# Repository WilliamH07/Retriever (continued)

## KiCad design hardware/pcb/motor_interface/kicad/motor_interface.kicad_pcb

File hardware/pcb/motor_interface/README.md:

# motor_interface

> **v2.0-draft — do not fabricate before M7, HALL_OC, P1, P2, P3.** Schematic and
> layout generated, ERC and DRC clean (ERC 0, DRC 0 with schematic parity and all severities, 0 unconnected). Every choice and its reason:
> [`decisions.md`](decisions.md) (French). Brief:
> [`cahier-des-charges.md`](cahier-des-charges.md).

| | |
|---|---|
| Size | 100 × 100 mm, 4 layers, 4 × M3, antenna notch on the right edge |
| Parts | 123 placed by the assembler (117 SMD + 6 Micro-Fit 6-way); hand-soldered: 2 × Micro-Fit 8-way, 2 × Mill-Max sockets; 14 option footprints not fitted; 20 named test pads |
| Module | ESP32-DevKitC V4 on two 1 × 19 turned-pin sockets, rows 25.40 mm apart (P1 to confirm) |
| Sources | [`kicad/`](kicad/) — KiCad 10 project, **generated** by [`scripts/build.py`](scripts/build.py) |
| Fabrication | [`fab/`](fab/) — Gerber zip, JLCPCB BOM and placement, schematic PDF, renders |

Rebuild everything: `./build.sh` (routing takes several minutes) then `./fab.sh`
(needs the toolchain in [`../outils.md`](../outils.md)). Do not edit the KiCad files
by hand: change `scripts/build.py` and rebuild.

Sits between a MOTION ESP32 and two ZS-X11H drivers with their hub motors. One
reference, two boards in service (front and rear), three spares from a lot of five.
The role is set by a solder jumper read through the ADS1115, not by GPIO straps.

The specification of record is
[`10-spec-motor-interface.md`](../../../docs/architecture/10-spec-motor-interface.md).
The earlier four-motor board is archived in
[`docs/archive/pcb-v1/`](../../../docs/archive/pcb-v1/).

## What changed against the specification (13 November 2026)

| Point | Spec / ICD v1.2 | This board | Why |
|---|---|---|---|
| `5V_BRAKE` | through J5/J6 pin 7, 2200 µF on board | **not on this board**, pin 7 NC | Decision D5: unplugging the board must keep the brake applied |
| Power input | J7 and trunk pin 1 | **trunk only**, J7 removed | One source, nothing to arbitrate |
| Grounds | undefined | **`GND`, `GND_MOT_A`, `GND_MOT_B` kept apart**, bench-only 0 Ω ties not fitted | Decision D4: single star point on `safety_power` |
| DAC supply | 5 V | **3.3 V**, internal 2.048 V reference, op-amp gain 2.5 | `MCP4728` VIH = 0.7 VDD, unreachable from a 3.3 V bus at 5 V |
| Low-side switches | `DMG1012T` (SOT-523) | **`AO3400A`** (SOT-23, JLCPCB basic) | 48 mΩ guaranteed at VGS 2.5 V, hand-reworkable |
| Polarity options | on `DIR`, `STOP`, `EL` | **`DIR` and `STOP` only** | Any option on `EL` could defeat the fail-safe |
| Hall PPTC | 30 mA on the pull-up tap | **removed** | Separate `+5V_MOT_A/B` nets; no PPTC of that size trips before the 78L05 |
| Hall activity LEDs | six | **none** | Test points and the serial console do the same job |

## Scope

| Function | Implementation |
|---|---|
| Hall passthrough | J1→J3, J2→J4: five straight 0.8 mm tracks each, one layer, no via, no part in series |
| Hall tap | 2.2 kΩ pull-up (population option, HALL_OC), 2.2 kΩ + 10 nF / 100 V, `BAT54S` clamp, referenced to `GND_MOT_x`; `SN74LVC3G17` at 3.3 V (Ioff) |
| Speed command | `MCP4728` (3.3 V, internal ref.) → `TLV9062` ×2.5 → `VR`, 0 V with the module out |
| `DIR`, `STOP` | `AO3400A` open drain, gate pull-down; pull-up / pull-down / direct-drive footprints not fitted |
| Brake `EL` | per wheel `74LVC1G08` (`GPIO26` AND `/SAFE`) → `AO3400A`; pull-up on the harness |
| Temperatures, role, revision | `ADS1115` at 0x48: NTC A, NTC B, role divider (SJ1/SJ2), revision divider (½ = v2.0) |
| Watchdog | `TPL5010`, 2 s, `RSTn` on the module `EN` (D7) |
| CAN | `TCAN1042HVDR`, `STB` grounded, `VIO` 3.3 V, `NUP2105L`, `ACT45B`, no termination |
| Power | trunk 5 V → `AO3401A` reverse protection → `SMAJ6.0A` → `LM66100` → module 5 V; 3.3 V from the module |

## Blocking measurements

M7 (Hall output level and impedance), HALL_OC (open collector or push-pull),
HALL_COL (wire colours, silkscreen), P1 to P3 on the ESP32 module (row spacing, pin
order, PSRAM variant). See [`docs/measurements/`](../../../docs/measurements/).

Pinout: `boards.motor_interface` in [`hardware/icd.yaml`](../../icd.yaml) (v1.3; the
changes this board brought to v1.3 are listed at the end of [`decisions.md`](decisions.md)).

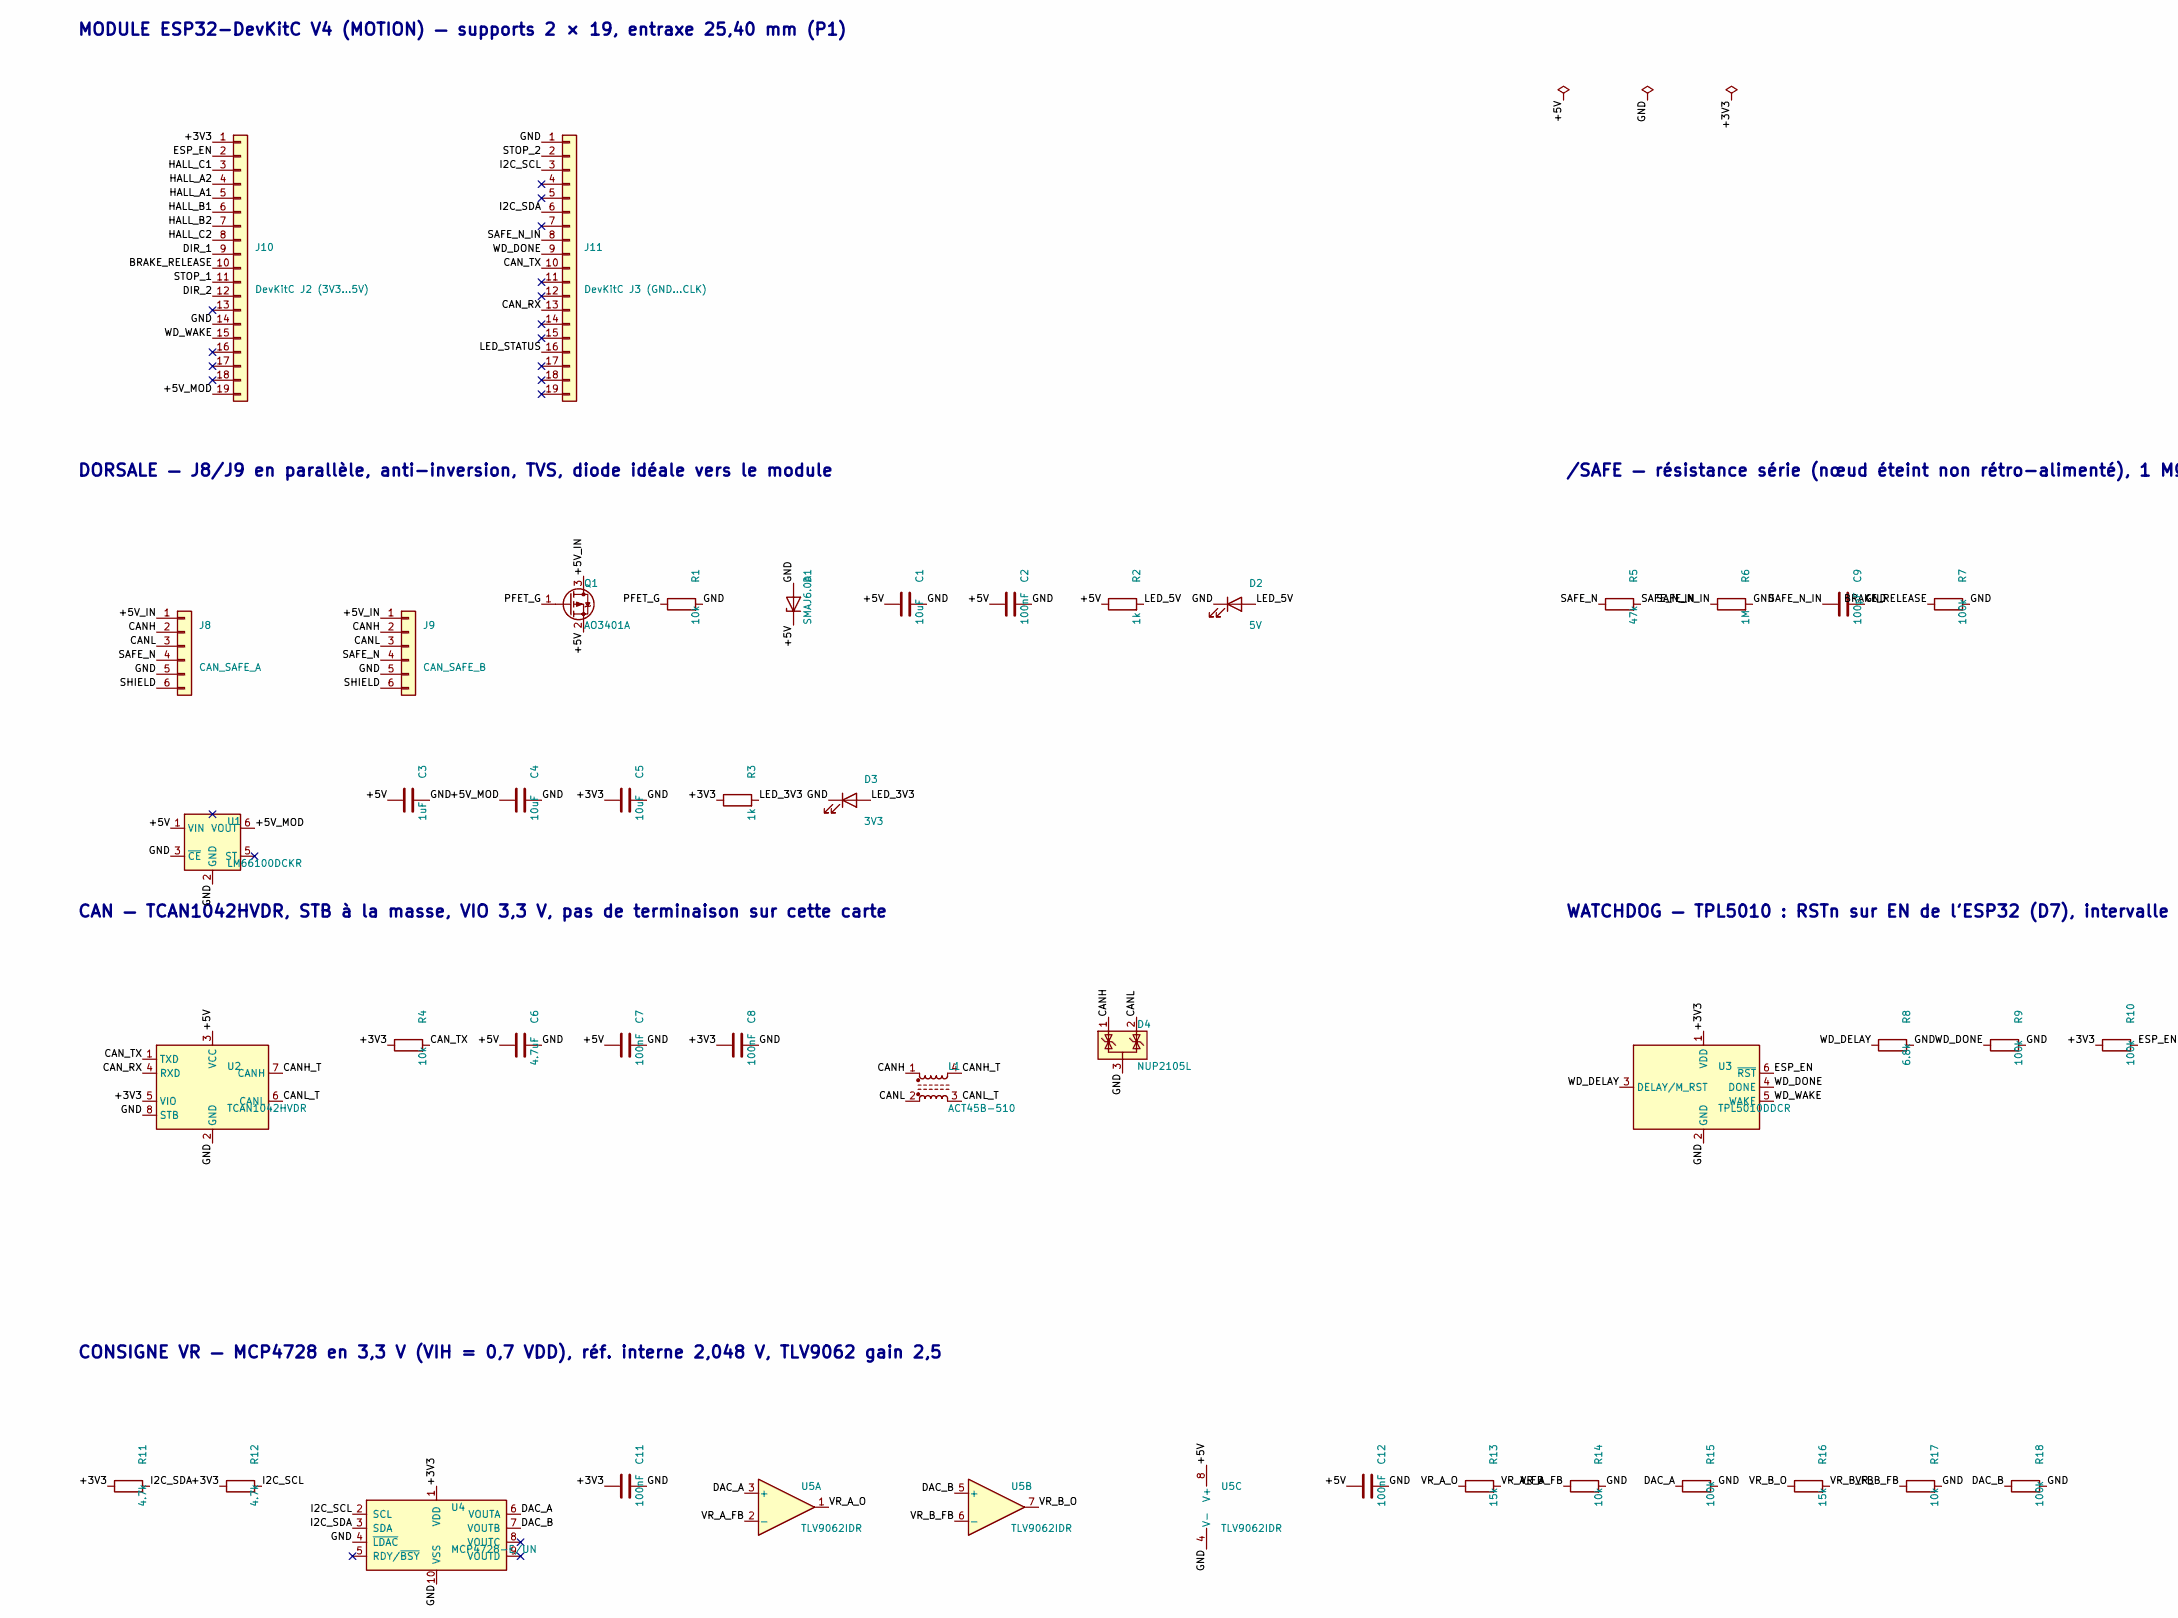
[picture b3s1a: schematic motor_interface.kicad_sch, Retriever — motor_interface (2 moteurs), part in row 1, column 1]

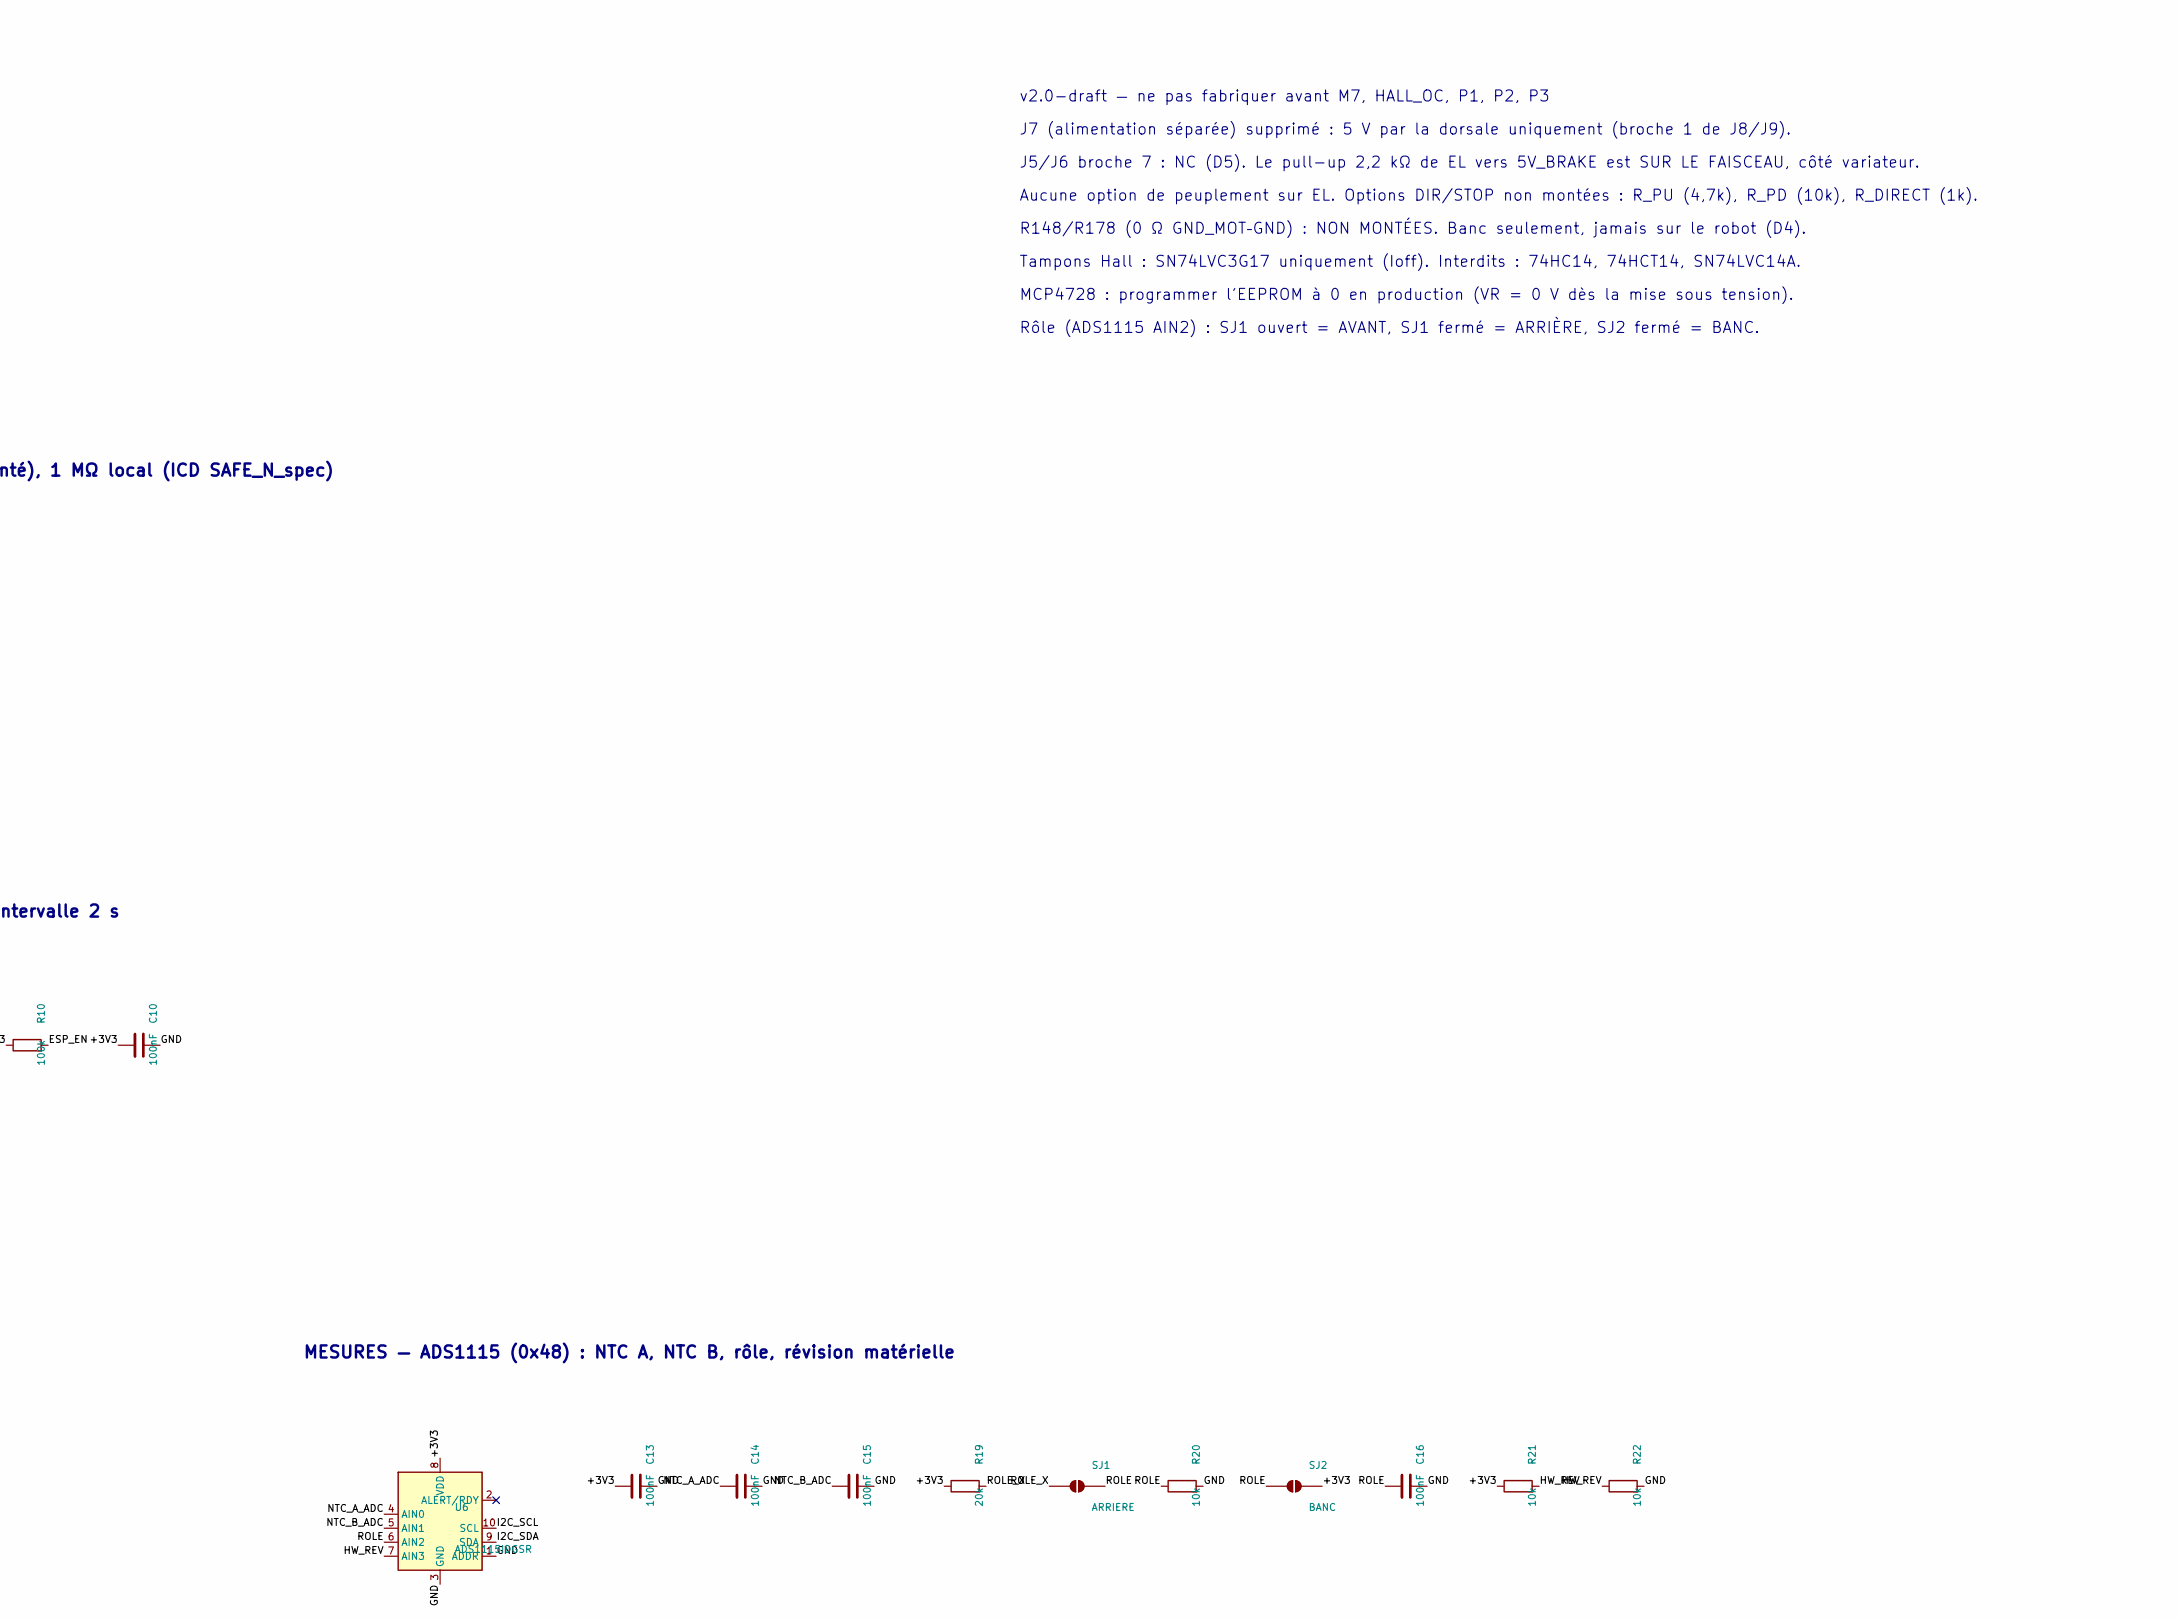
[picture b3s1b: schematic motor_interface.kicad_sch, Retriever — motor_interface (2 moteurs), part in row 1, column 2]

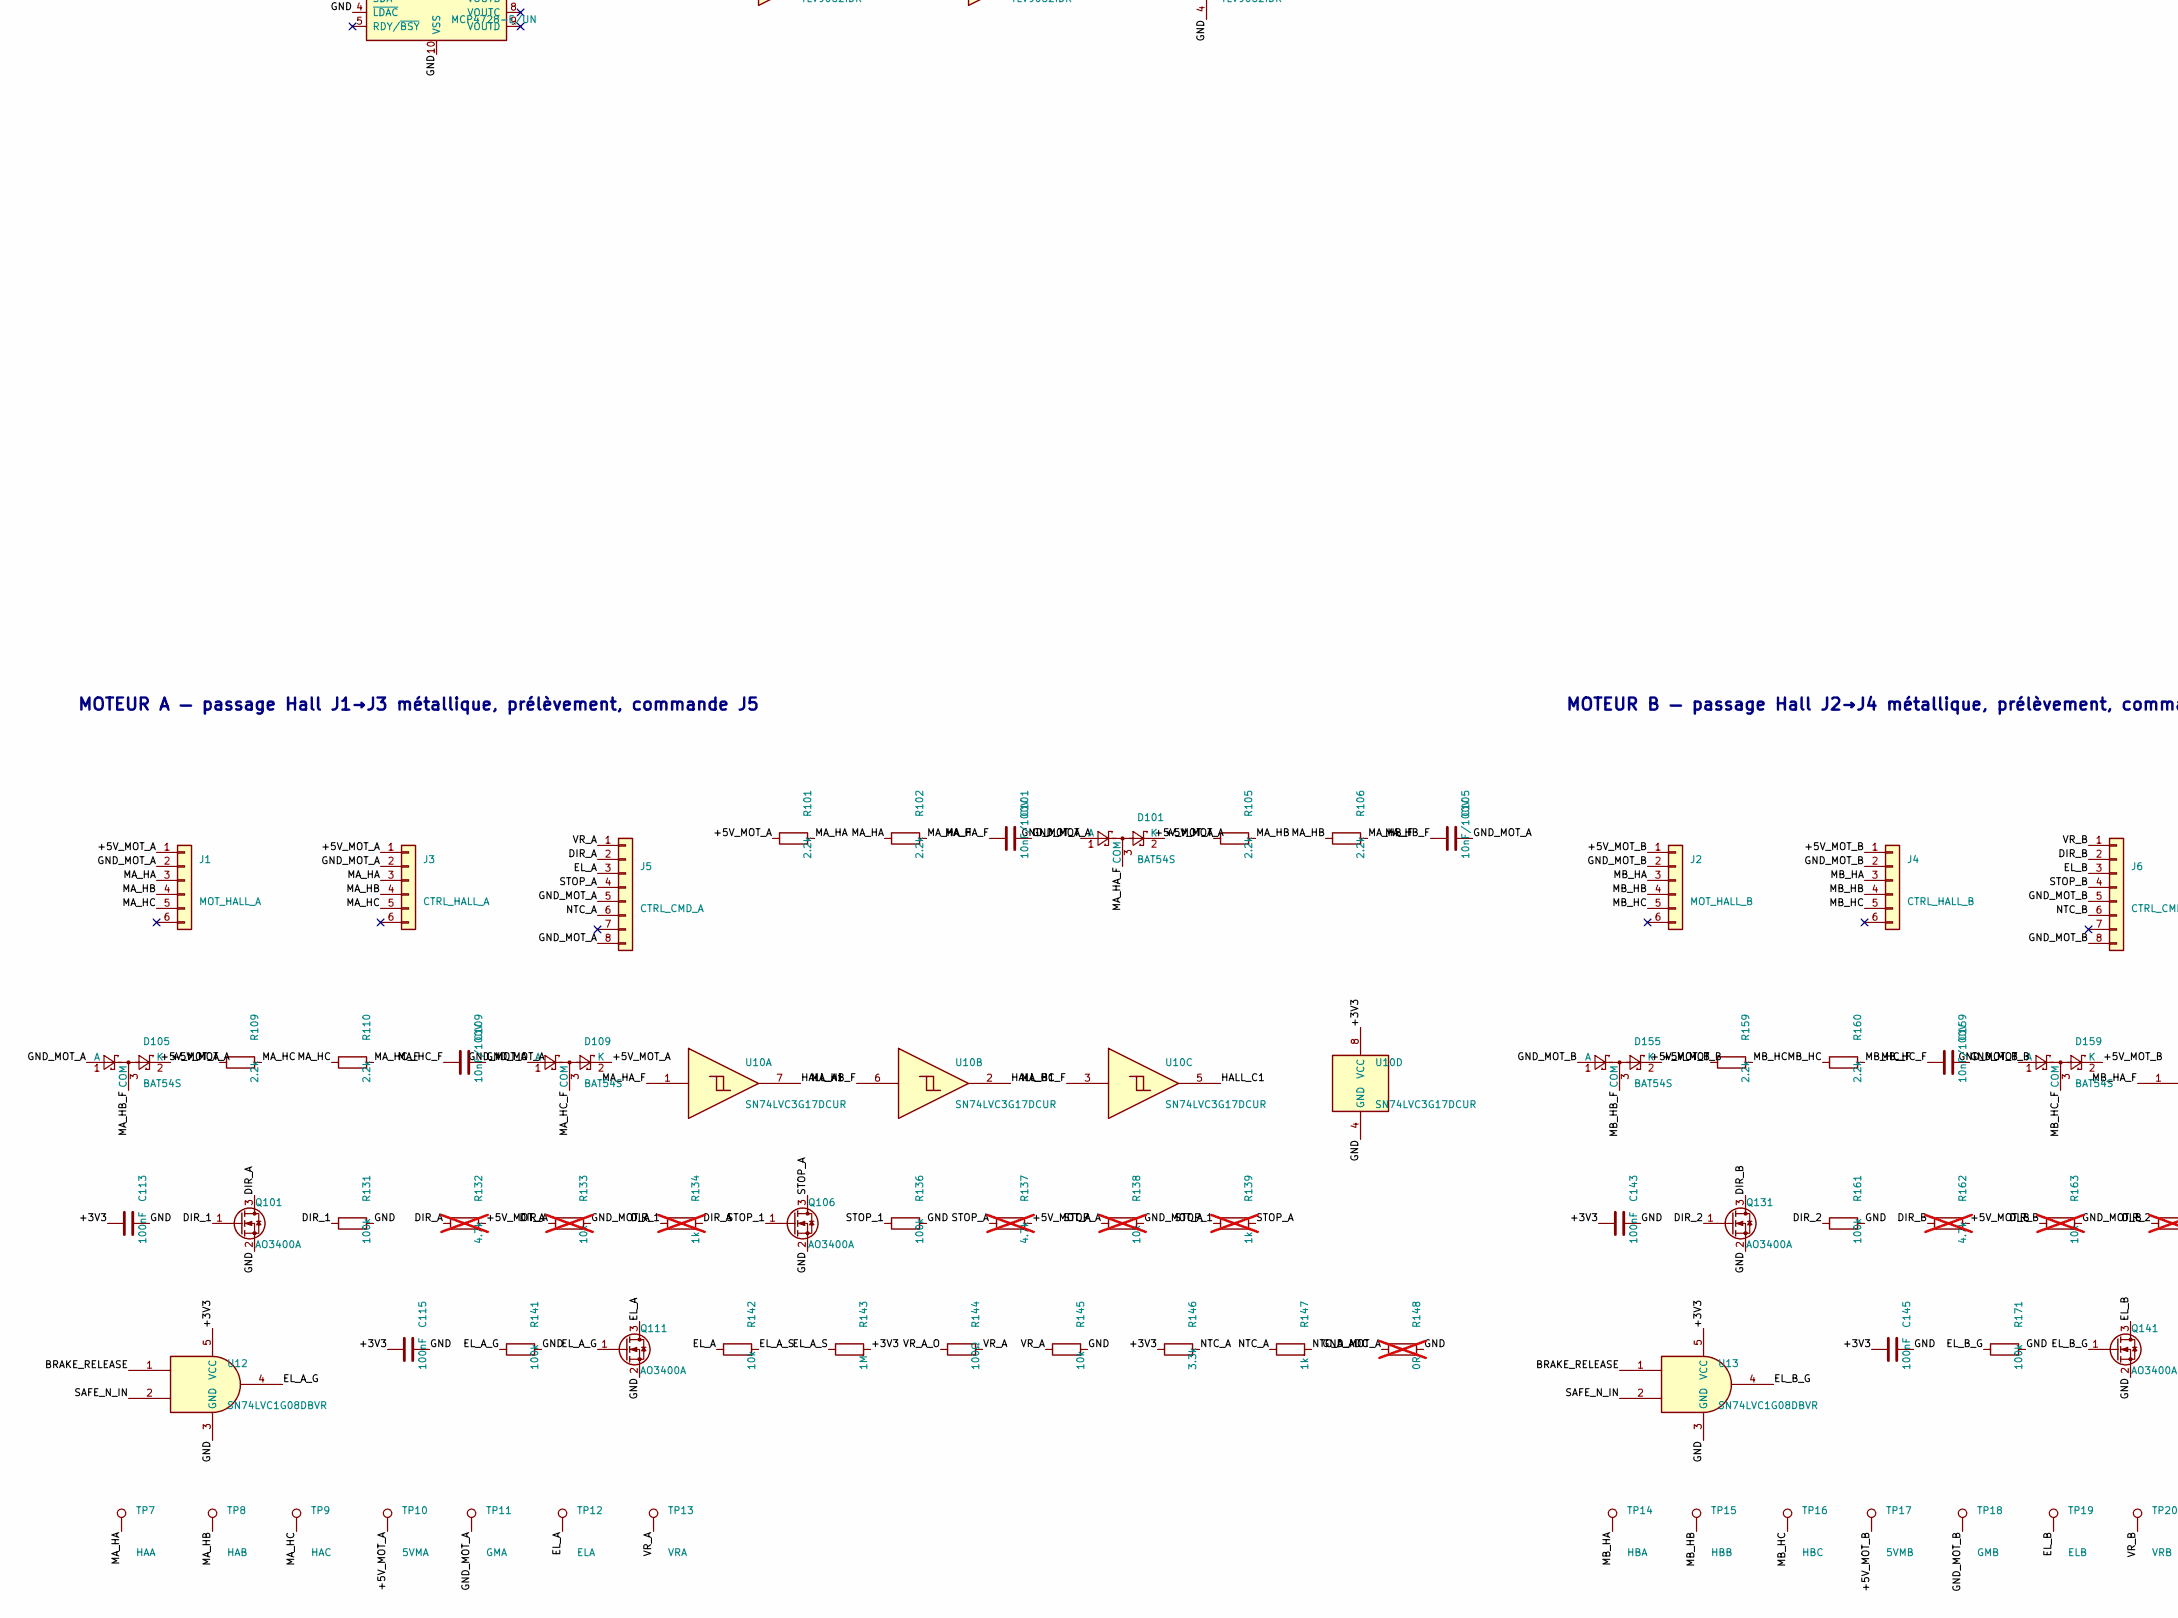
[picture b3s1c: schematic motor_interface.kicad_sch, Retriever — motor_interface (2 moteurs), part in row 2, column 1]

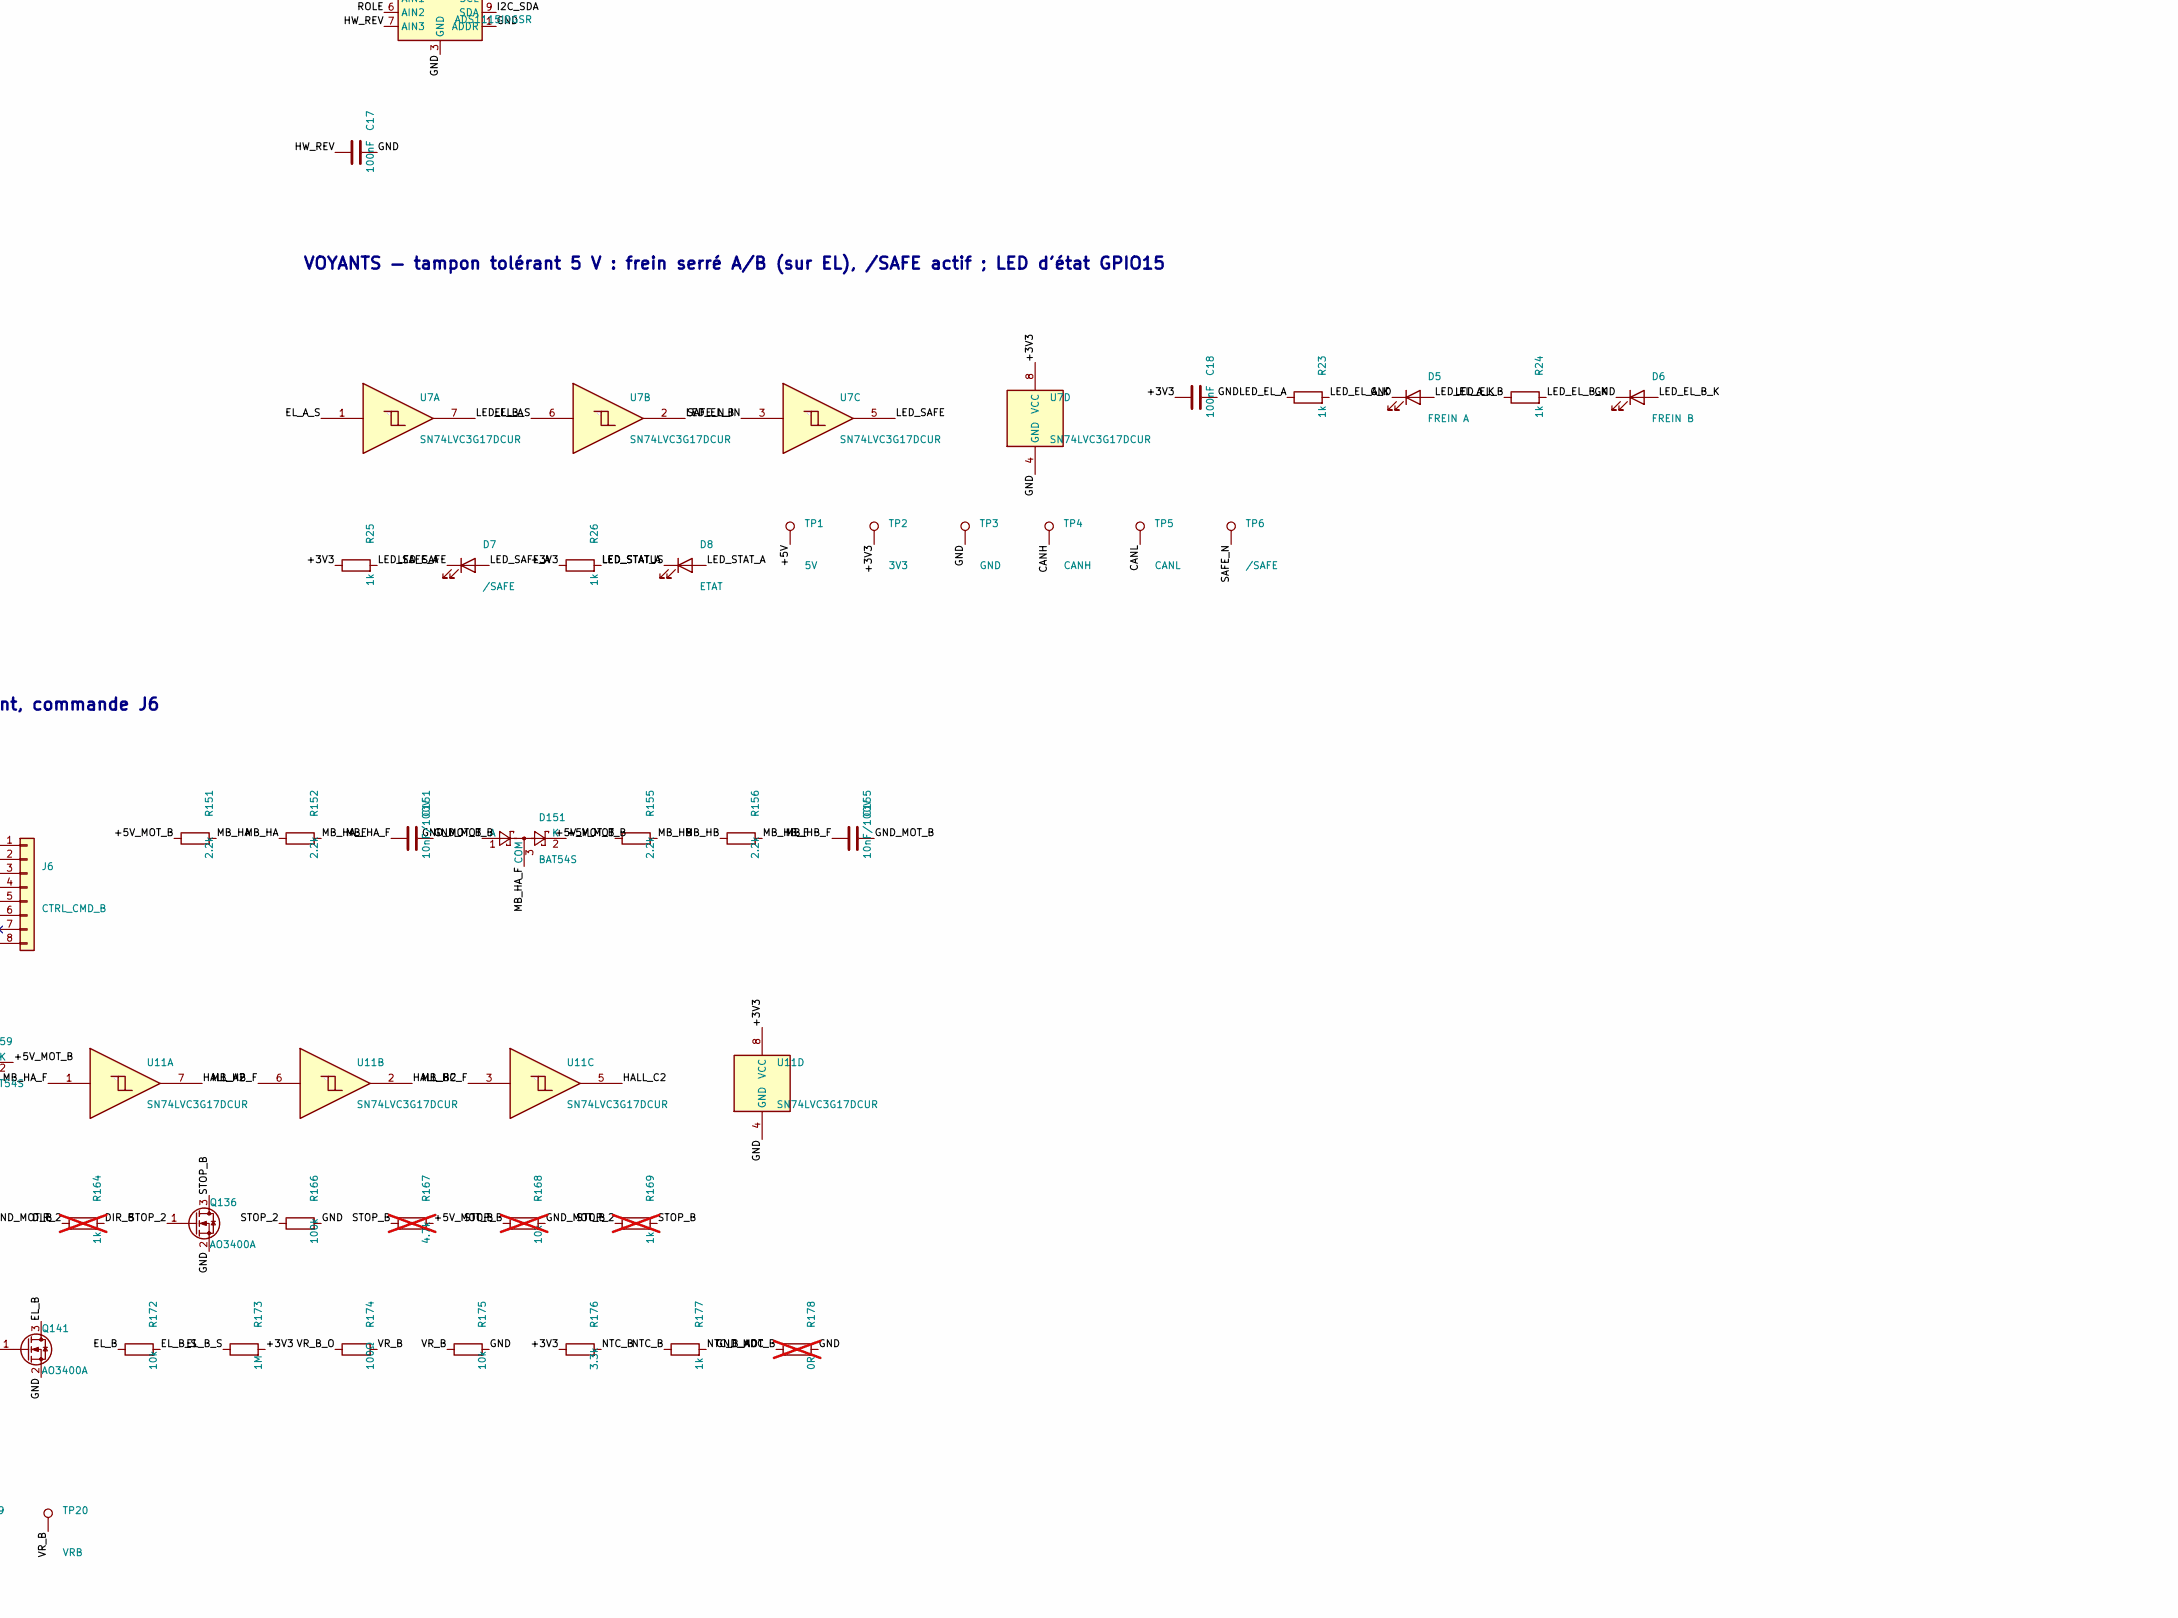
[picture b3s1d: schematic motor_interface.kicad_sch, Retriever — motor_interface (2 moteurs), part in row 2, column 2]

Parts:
C1, C4, C5: 10uF; C_0805_2012Metric; MPN CL21A106KAYNNNE; LCSC C15850
C2, C7, C8, C10, C11, C12, C13, C14, C15, C16, C17, C18, C113, C115, C143, C145: 100nF; C_0603_1608Metric; MPN CC0603KRX7R9BB104; LCSC C14663
C3: 1uF; C_0603_1608Metric; MPN CL10A105KB8NNNC; LCSC C15849
C6: 4.7uF; C_0805_2012Metric; MPN CL21A475KAQNNNE; LCSC C1779
C9: 100pF; C_0603_1608Metric; MPN CC0603JRNPO9BN101; LCSC C14858
C101, C105, C109, C151, C155, C159: 10nF/100V; C_0603_1608Metric; MPN FH 0603B103K101NT; LCSC C43253
D1: SMAJ6.0A; D_SMA; MPN Littelfuse SMAJ6.0A; LCSC C223993
D2: 5V; LED_0603_1608Metric; MPN Everlight 19-217/GHC; LCSC C72043
D3: 3V3; LED_0603_1608Metric; MPN Everlight 19-217/GHC; LCSC C72043
D4: NUP2105L; SOT-23; MPN onsemi NUP2105LT1G; LCSC C14486
D5: FREIN A; LED_0603_1608Metric; MPN Hubei KENTO KT-0603R; LCSC C2286
D6: FREIN B; LED_0603_1608Metric; MPN Hubei KENTO KT-0603R; LCSC C2286
D7: /SAFE; LED_0603_1608Metric; MPN Hubei KENTO KT-0603R; LCSC C2286
D8: ETAT; LED_0603_1608Metric; MPN Everlight 19-217/BHC; LCSC C72041
D101, D105, D109, D151, D155, D159: BAT54S; SOT-23; MPN Nexperia BAT54S,215; LCSC C47546
J1: MOT_HALL_A; Molex_Micro-Fit_3.0_43650-0615_1x06_P3.00mm_Vertical; MPN Molex 43650-0615; LCSC C505231
J2: MOT_HALL_B; Molex_Micro-Fit_3.0_43650-0615_1x06_P3.00mm_Vertical; MPN Molex 43650-0615; LCSC C505231
J3: CTRL_HALL_A; Molex_Micro-Fit_3.0_43650-0615_1x06_P3.00mm_Vertical; MPN Molex 43650-0615; LCSC C505231
J4: CTRL_HALL_B; Molex_Micro-Fit_3.0_43650-0615_1x06_P3.00mm_Vertical; MPN Molex 43650-0615; LCSC C505231
J5: CTRL_CMD_A; Molex_Micro-Fit_3.0_43650-0815_1x08_P3.00mm_Vertical; MPN Molex 43650-0815 (Mouser 538-43650-0815)
J6: CTRL_CMD_B; Molex_Micro-Fit_3.0_43650-0815_1x08_P3.00mm_Vertical; MPN Molex 43650-0815 (Mouser 538-43650-0815)
J8: CAN_SAFE_A; Molex_Micro-Fit_3.0_43650-0615_1x06_P3.00mm_Vertical; MPN Molex 43650-0615; LCSC C505231
J9: CAN_SAFE_B; Molex_Micro-Fit_3.0_43650-0615_1x06_P3.00mm_Vertical; MPN Molex 43650-0615; LCSC C505231
J10: DevKitC J2 (3V3…5V); PinSocket_1x19_P2.54mm_Vertical; MPN Mill-Max 310-43-119-41-001000 (Mouser)
J11: DevKitC J3 (GND…CLK); PinSocket_1x19_P2.54mm_Vertical; MPN Mill-Max 310-43-119-41-001000 (Mouser)
L1: ACT45B-510; IND-SMD_4P-L4.5-W3.2-TL; MPN TDK ACT45B-510-2P-TL003; LCSC C76584
Q1: AO3401A; SOT-23; MPN AOS AO3401A; LCSC C15127
Q101, Q106, Q111, Q131, Q136, Q141: AO3400A; SOT-23; MPN AOS AO3400A; LCSC C20917
R1, R4, R14, R17, R20, R21, R22, R142, R145, R172, R175: 10k; R_0603_1608Metric; MPN 0603WAF1002T5E; LCSC C25804
R2, R3, R23, R24, R25, R26, R147, R177: 1k; R_0603_1608Metric; MPN 0603WAF1001T5E; LCSC C21190
R5: 47k; R_0603_1608Metric; MPN 0603WAF4702T5E; LCSC C25819
R6, R143, R173: 1M; R_0603_1608Metric; MPN 0603WAF1004T5E; LCSC C22935
R7, R9, R10, R15, R18, R131, R136, R141, R161, R166, R171: 100k; R_0603_1608Metric; MPN 0603WAF1003T5E; LCSC C25803
R8: 6.8k; R_0603_1608Metric; MPN 0603WAF6801T5E; LCSC C23212
R11, R12: 4.7k; R_0603_1608Metric; MPN 0603WAF4701T5E; LCSC C23162
R13, R16: 15k; R_0603_1608Metric; MPN 0603WAF1502T5E; LCSC C22809
R19: 20k; R_0603_1608Metric; MPN 0603WAF2002T5E; LCSC C4184
R101, R102, R105, R106, R109, R110, R151, R152, R155, R156, R159, R160: 2.2k; R_0603_1608Metric; MPN 0603WAF2201T5E; LCSC C4190
R132, R137, R162, R167: 4.7k; R_0603_1608Metric; MPN 0603WAF4701T5E; LCSC C23162; not fitted
R133, R138, R163, R168: 10k; R_0603_1608Metric; MPN 0603WAF1002T5E; LCSC C25804; not fitted
R134, R139, R164, R169: 1k; R_0603_1608Metric; MPN 0603WAF1001T5E; LCSC C21190; not fitted
R144, R174: 100Ω; R_0603_1608Metric; MPN 0603WAF1000T5E; LCSC C22775
R146, R176: 3.3k; R_0603_1608Metric; MPN 0603WAF3301T5E; LCSC C22978
R148, R178: 0R; R_0603_1608Metric; MPN 0603WAF0000T5E; LCSC C21189; not fitted
SJ1: ARRIERE; SolderJumper-2_P1.3mm_Open_RoundedPad1.0x1.5mm
SJ2: BANC; SolderJumper-2_P1.3mm_Open_RoundedPad1.0x1.5mm
TP1: 5V; TestPoint_Pad_D1.5mm
TP2: 3V3; TestPoint_Pad_D1.5mm
TP3: GND; TestPoint_Pad_D1.5mm
TP4: CANH; TestPoint_Pad_D1.5mm
TP5: CANL; TestPoint_Pad_D1.5mm
TP6: /SAFE; TestPoint_Pad_D1.5mm
TP7: HAA; TestPoint_Pad_D1.5mm
TP8: HAB; TestPoint_Pad_D1.5mm
TP9: HAC; TestPoint_Pad_D1.5mm
TP10: 5VMA; TestPoint_Pad_D1.5mm
TP11: GMA; TestPoint_Pad_D1.5mm
TP12: ELA; TestPoint_Pad_D1.5mm
TP13: VRA; TestPoint_Pad_D1.5mm
TP14: HBA; TestPoint_Pad_D1.5mm
TP15: HBB; TestPoint_Pad_D1.5mm
TP16: HBC; TestPoint_Pad_D1.5mm
TP17: 5VMB; TestPoint_Pad_D1.5mm
TP18: GMB; TestPoint_Pad_D1.5mm
TP19: ELB; TestPoint_Pad_D1.5mm
TP20: VRB; TestPoint_Pad_D1.5mm
U1: LM66100DCKR; SOT-363_SC-70-6; MPN TI LM66100DCKR; LCSC C2869734
U2: TCAN1042HVDR; SOIC-8_3.9x4.9mm_P1.27mm; MPN TI TCAN1042HVDR; LCSC C127869
U3: TPL5010DDCR; SOT-23-6; MPN TI TPL5010DDCR; LCSC C473912
U4: MCP4728-E/UN; MSOP-10_3x3mm_P0.5mm; MPN Microchip MCP4728-E/UN; LCSC C108207
U5: TLV9062IDR; SOIC-8_3.9x4.9mm_P1.27mm; MPN TI TLV9062IDR; LCSC C398355
U6: ADS1115IDGSR; TSSOP-10_3x3mm_P0.5mm; MPN TI ADS1115IDGSR; LCSC C37593
U7, U10, U11: SN74LVC3G17DCUR; VSSOP-8_2.3x2mm_P0.5mm; MPN TI SN74LVC3G17DCUR; LCSC C68245
U12, U13: SN74LVC1G08DBVR; SOT-23-5; MPN TI SN74LVC1G08DBVR; LCSC C7666

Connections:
/+3V3: C5.1, C8.1, C10.1, C11.1, C13.1, C18.1, C113.1, C115.1, C143.1, C145.1, J10.1, R3.1, R4.1, R10.1, R11.1, R12.1, R19.1, R21.1, R25.1, R26.1, R143.2, R146.1, R173.2, R176.1, SJ2.2 (B), TP2.1, U2.5 (VIO), U3.1 (VDD), U4.1 (VDD), U6.8 (VDD), U7.8 (VCC), U10.8 (VCC), U11.8 (VCC), U12.5 (VCC), U13.5 (VCC)
/+5V: C1.1, C2.1, C3.1, C6.1, C7.1, C12.1, D1.1 (K), Q1.2 (S), R2.1, TP1.1, U1.1 (VIN), U2.3 (VCC), U5.8 (V+)
/+5V_IN: J8.1, J9.1, Q1.3 (D)
/+5V_MOD: C4.1, J10.19, U1.6 (VOUT)
/+5V_MOT_A: D101.2 (K), D105.2 (K), D109.2 (K), J1.1, J3.1, R101.1, R105.1, R109.1, R132.2, R137.2, TP10.1
/+5V_MOT_B: D151.2 (K), D155.2 (K), D159.2 (K), J2.1, J4.1, R151.1, R155.1, R159.1, R162.2, R167.2, TP17.1
/BRAKE_RELEASE: J10.10, R7.1, U12.1, U13.1
/CANH: D4.1 (K), J8.2, J9.2, L1.1, TP4.1
/CANH_T: L1.4, U2.7 (CANH)
/CANL: D4.2 (K), J8.3, J9.3, L1.2, TP5.1
/CANL_T: L1.3, U2.6 (CANL)
/CAN_RX: J11.13, U2.4 (RXD)
/CAN_TX: J11.10, R4.2, U2.1 (TXD)
/DAC_A: R15.1, U4.6 (VOUTA), U5.3 (+)
/DAC_B: R18.1, U4.7 (VOUTB), U5.5 (+)
/DIR_1: J10.9, Q101.1 (G), R131.1, R134.1
/DIR_2: J10.12, Q131.1 (G), R161.1, R164.1
/DIR_A: J5.2, Q101.3 (D), R132.1, R133.1, R134.2
/DIR_B: J6.2, Q131.3 (D), R162.1, R163.1, R164.2
/EL_A: J5.3, Q111.3 (D), R142.1, TP12.1
/EL_A_G: Q111.1 (G), R141.1, U12.4
/EL_A_S: R142.2, R143.1, U7.1
/EL_B: J6.3, Q141.3 (D), R172.1, TP19.1
/EL_B_G: Q141.1 (G), R171.1, U13.4
/EL_B_S: R172.2, R173.1, U7.6
/ESP_EN: J10.2, R10.2, U3.6 (~RST)
/GND: C1.2, C2.2, C3.2, C4.2, C5.2, C6.2, C7.2, C8.2, C9.2, C10.2, C11.2, C12.2, C13.2, C14.2, C15.2, C16.2, C17.2, C18.2, C113.2, C115.2, C143.2, C145.2, D1.2 (A), D2.1 (K), D3.1 (K), D4.3 (A), D5.1 (K), D6.1 (K), J8.5, J9.5, J10.14, J11.1, Q101.2 (S), Q106.2 (S), Q111.2 (S), Q131.2 (S), Q136.2 (S), Q141.2 (S), R1.2, R6.2, R7.2, R8.2, R9.2, R14.2, R15.2, R17.2, R18.2, R20.2, R22.2, R131.2, R136.2, R141.2, R145.2, R148.2, R161.2, R166.2, R171.2, R175.2, R178.2, TP3.1, U1.2 (GND), U1.3 (~CE), U2.2 (GND), U2.8 (STB), U3.2 (GND), U4.4 (~LDAC), U4.10 (VSS), U5.4 (V-), U6.1 (ADDR), U6.3 (GND), U7.4 (GND), U10.4 (GND), U11.4 (GND), U12.3 (GND), U13.3 (GND)
/GND_MOT_A: C101.2, C105.2, C109.2, D101.1 (A), D105.1 (A), D109.1 (A), J1.2, J3.2, J5.5, J5.8, R133.2, R138.2, R148.1, TP11.1
/GND_MOT_B: C151.2, C155.2, C159.2, D151.1 (A), D155.1 (A), D159.1 (A), J2.2, J4.2, J6.5, J6.8, R163.2, R168.2, R178.1, TP18.1
/HALL_A1: J10.5, U10.7
/HALL_A2: J10.4, U11.7
/HALL_B1: J10.6, U10.2
/HALL_B2: J10.7, U11.2
/HALL_C1: J10.3, U10.5
/HALL_C2: J10.8, U11.5
/HW_REV: C17.1, R21.2, R22.1, U6.7 (AIN3)
/I2C_SCL: J11.3, R12.2, U4.2 (SCL), U6.10 (SCL)
/I2C_SDA: J11.6, R11.2, U4.3 (SDA), U6.9 (SDA)
/LED_3V3: D3.2 (A), R3.2
/LED_5V: D2.2 (A), R2.2
/LED_EL_A: R23.1, U7.7
/LED_EL_A_K: D5.2 (A), R23.2
/LED_EL_B: R24.1, U7.2
/LED_EL_B_K: D6.2 (A), R24.2
/LED_SAFE: D7.1 (K), U7.5
/LED_SAFE_A: D7.2 (A), R25.2
/LED_STATUS: D8.1 (K), J11.16
/LED_STAT_A: D8.2 (A), R26.2
/MA_HA: J1.3, J3.3, R101.2, R102.1, TP7.1
/MA_HA_F: C101.1, D101.3 (COM), R102.2, U10.1
/MA_HB: J1.4, J3.4, R105.2, R106.1, TP8.1
/MA_HB_F: C105.1, D105.3 (COM), R106.2, U10.6
/MA_HC: J1.5, J3.5, R109.2, R110.1, TP9.1
/MA_HC_F: C109.1, D109.3 (COM), R110.2, U10.3
/MB_HA: J2.3, J4.3, R151.2, R152.1, TP14.1
/MB_HA_F: C151.1, D151.3 (COM), R152.2, U11.1
/MB_HB: J2.4, J4.4, R155.2, R156.1, TP15.1
/MB_HB_F: C155.1, D155.3 (COM), R156.2, U11.6
/MB_HC: J2.5, J4.5, R159.2, R160.1, TP16.1
/MB_HC_F: C159.1, D159.3 (COM), R160.2, U11.3
/NTC_A: J5.6, R146.2, R147.1
/NTC_A_ADC: C14.1, R147.2, U6.4 (AIN0)
/NTC_B: J6.6, R176.2, R177.1
/NTC_B_ADC: C15.1, R177.2, U6.5 (AIN1)
/PFET_G: Q1.1 (G), R1.1
/ROLE: C16.1, R20.1, SJ1.2 (B), SJ2.1 (A), U6.6 (AIN2)
/ROLE_X: R19.2, SJ1.1 (A)
/SAFE_N: J8.4, J9.4, R5.1, TP6.1
/SAFE_N_IN: C9.1, J11.8, R5.2, R6.1, U7.3, U12.2, U13.2
/SHIELD: J8.6, J9.6
/STOP_1: J10.11, Q106.1 (G), R136.1, R139.1
/STOP_2: J11.2, Q136.1 (G), R166.1, R169.1
/STOP_A: J5.4, Q106.3 (D), R137.1, R138.1, R139.2
/STOP_B: J6.4, Q136.3 (D), R167.1, R168.1, R169.2
/VR_A: J5.1, R144.2, R145.1, TP13.1
/VR_A_FB: R13.2, R14.1, U5.2 (-)
/VR_A_O: R13.1, R144.1, U5.1
/VR_B: J6.1, R174.2, R175.1, TP20.1
/VR_B_FB: R16.2, R17.1, U5.6 (-)
/VR_B_O: R16.1, R174.1, U5.7
/WD_DELAY: R8.1, U3.3 (DELAY/M_RST)
/WD_DONE: J11.9, R9.1, U3.4 (DONE)
/WD_WAKE: J10.15, U3.5 (WAKE)

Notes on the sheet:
MODULE ESP32-DevKitC V4 (MOTION) — supports 2 × 19, entraxe 25,40 mm (P1)
DORSALE — J8/J9 en parallèle, anti-inversion, TVS, diode idéale vers le module
CAN — TCAN1042HVDR, STB à la masse, VIO 3,3 V, pas de terminaison sur cette carte
/SAFE — résistance série (nœud éteint non rétro-alimenté), 1 MΩ local (ICD SAFE_N_spec)
WATCHDOG — TPL5010 : RSTn sur EN de l'ESP32 (D7), intervalle 2 s
CONSIGNE VR — MCP4728 en 3,3 V (VIH = 0,7 VDD), réf. interne 2,048 V, TLV9062 gain 2,5
MESURES — ADS1115 (0x48) : NTC A, NTC B, rôle, révision matérielle
VOYANTS — tampon tolérant 5 V : frein serré A/B (sur EL), /SAFE actif ; LED d'état GPIO15
MOTEUR A — passage Hall J1→J3 métallique, prélèvement, commande J5
MOTEUR B — passage Hall J2→J4 métallique, prélèvement, commande J6
v2.0-draft — ne pas fabriquer avant M7, HALL_OC, P1, P2, P3
J7 (alimentation séparée) supprimé : 5 V par la dorsale uniquement (broche 1 de J8/J9).
J5/J6 broche 7 : NC (D5). Le pull-up 2,2 kΩ de EL vers 5V_BRAKE est SUR LE FAISCEAU, côté variateur.
Aucune option de peuplement sur EL. Options DIR/STOP non montées : R_PU (4,7k), R_PD (10k), R_DIRECT (1k).
R148/R178 (0 Ω GND_MOT–GND) : NON MONTÉES. Banc seulement, jamais sur le robot (D4).
Tampons Hall : SN74LVC3G17 uniquement (Ioff). Interdits : 74HC14, 74HCT14, SN74LVC14A.
MCP4728 : programmer l'EEPROM à 0 en production (VR = 0 V dès la mise sous tension).
Rôle (ADS1115 AIN2) : SJ1 ouvert = AVANT, SJ1 fermé = ARRIÈRE, SJ2 fermé = BANC.
